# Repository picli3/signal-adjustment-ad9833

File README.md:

# Ajustador de señal DDS (AD9833)
El modulo AD9833 es capaz de general señales para ser usadas para diversas aplicaciones, sin embargo, esta señal siempre es continua, es por esta razon que implemente este circuito, el cual consistene en llevar la señal a valores negativos, ademas de aumentar la ganancia de la señal de salida.

## Diagrama de bloques

El bloque de **POWER** esta porque con eso se genera un voltage negativo de **-5V** para el amplificador operacional, en este caso el **LM358**

## PCB
Todo el circuito esta en una cara asi que sera facil soldar.

Los archivos de fabricacion los puedes descargar [aqui](https://github.com/picli3/signal-adjustment-ad9833/releases/download/v1.0.0/v1.0.0.zip)

Mas información [maykolrey.com](https://maykolrey.com)
[licencia](./LICENSE)

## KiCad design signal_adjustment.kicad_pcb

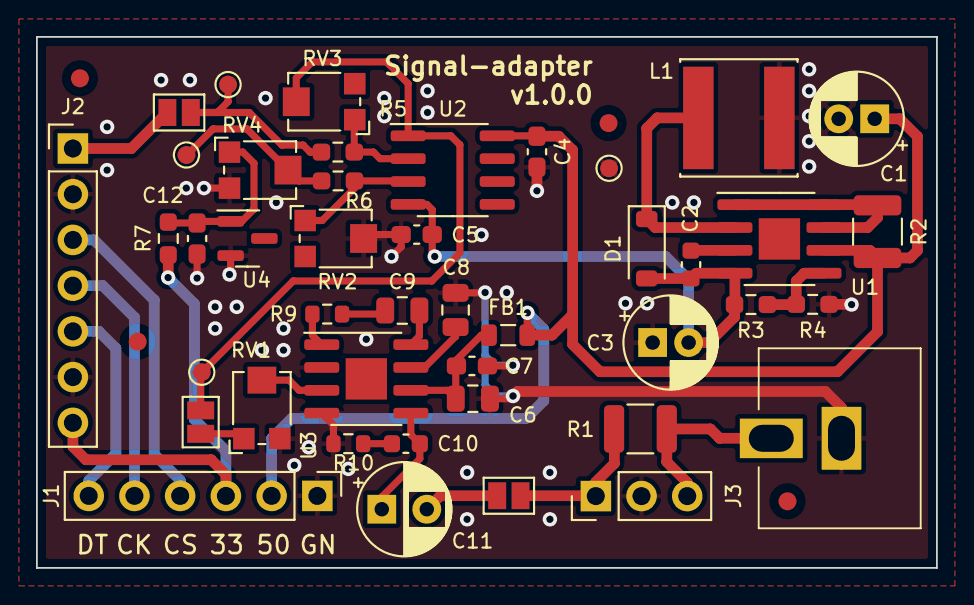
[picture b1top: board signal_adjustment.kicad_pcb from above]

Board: 2 copper layers, 50.0 x 29.5 mm, 47 parts (0 on the bottom side), 30 nets.

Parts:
C1, C3: 100u; CP_Radial_D5.0mm_P2.00mm
C2: 1n; C_0603_1608Metric
C4, C5, C7, C12: 100nF; C_0603_1608Metric_Pad1.08x0.95mm_HandSolder
C6, C8, C9: 10uF; C_0805_2012Metric
C10: 47nF; C_0603_1608Metric
C11: 220uF; CP_Radial_D5.0mm_P2.50mm
D1: 1N5819; D_SOD-123
FB1: 120@100MHz; L_0805_2012Metric
FID1, FID2, FID3, FID4: Fiducial; Fiducial_1mm_Mask2mm
J1: Conn_01x06; PinHeader_1x06_P2.54mm_Vertical
J2: AD9833; PinHeader_1x07_P2.54mm_Vertical
J3: Conn_01x03; PinHeader_1x03_P2.54mm_Vertical
J4: Conn_Coaxial; RCA-Av-8.4-5
JP1, JP2, JP3: Jumper_2_Open; SolderJumper-2_P1.3mm_Open_Pad1.0x1.5mm
L1: 100u; L_Changjiang_FNR6045S
R1: 2; R_1210_3225Metric
R2: 0.22; R_1210_3225Metric
R3, R7: 1k; R_0603_1608Metric_Pad0.98x0.95mm_HandSolder
R4: 3k; R_0603_1608Metric_Pad0.98x0.95mm_HandSolder
R5, R6: 10k; R_0603_1608Metric_Pad0.98x0.95mm_HandSolder
R9: 1.2k; R_0603_1608Metric
R10: 10; R_0603_1608Metric
RV1: 10k; Potentiometer_Bourns_TC33X_Vertical
RV2, RV3: 50k; Potentiometer_Bourns_TC33X_Vertical
RV4: 1k; Potentiometer_Bourns_TC33X_Vertical
TP1: VREF; TestPoint_Pad_D1.0mm
TP2: VIN; TestPoint_Pad_D1.0mm
TP3: VOUT; TestPoint_Pad_D1.0mm
TP4: GND; TestPoint_Pad_D1.0mm
U1: MC34063; HSOP-8-1EP_3.9x4.9mm_P1.27mm_EP2.3x2.3mm
U2: LM358; SOIC-8_3.9x4.9mm_P1.27mm
U3: LM386; HSOP-8-1EP_3.9x4.9mm_P1.27mm_EP2.3x2.3mm
U4: ADR510; SOT-23

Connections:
+3V3: J1.3, J2.7, R7.2
+5V: C1.1, C4.1, FB1.2, J1.2, R2.1, U1.6 (Vin), U2.8 (V+)
/Amplifier/INPUT: JP2.2 (B), RV1.1
/Amplifier/OUTPUT: C11.2, JP3.1 (A)
/SCLK: J1.5, J2.4
/SDATA: J1.6, J2.5
/S_OUT: J2.1, JP1.1 (A)
/leveling/-5V: C2.2, C3.2, C5.2, D1.2 (A), R3.2, U1.4 (GND), U2.4 (V-)
/leveling/SIGNAL_IN: JP1.2 (B), R5.2, TP2.1
/leveling/SIGNAL_OUT: JP2.1 (A), RV3.2, TP3.1, U2.1
/power/ref: R3.1, R4.1, U1.5 (Vfb)
/~CS: J1.4, J2.3
GND: C1.2, C3.1, C4.2, C5.1, C6.1, C7.1, C8.2, C12.2, J1.1, J2.2, J2.6, J3.2, J4.2 (Ext), L1.2, R4.2, R10.1, RV1.3, RV2.2, RV4.3, TP4.1, U3.2 (-), U3.4 (GND), U4.2
unnamed: C9.1, U3.8 (GAIN)
unnamed: C9.2, R9.1
unnamed: C10.1, R10.2
unnamed: C10.2, C11.1, U3.5
unnamed: C12.1, R7.1, RV4.1, U4.1
unnamed: D1.1 (K), L1.1, U1.2 (SwE)
unnamed: J3.1, JP3.2 (B), R1.1
unnamed: J3.3, J4.1 (In), R1.2
unnamed: R6.2, RV4.2, TP1.1
unnamed: R9.2, U3.1 (GAIN)
unnamed: R2.2, U1.1 (SwC), U1.7 (Ipk), U1.8 (DC)
unnamed: C2.1, U1.3 (TC)
unnamed: R6.1, RV2.1, U2.3 (+)
unnamed: R5.1, RV3.1, U2.2 (-)
unnamed: RV1.2, U3.3 (+)
unnamed: C8.1, U3.7 (BYPASS)
unnamed: C6.2, C7.2, FB1.1, U3.6 (V+)

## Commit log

2023-12-03 agregando primera interaccion
2023-12-03 primera version
2023-12-03 agregando readme y licencia
2023-12-03 corrigiendo error ortografico
2023-12-03 error en referencia
